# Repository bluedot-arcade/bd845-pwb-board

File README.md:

<p align="right">

</p>
<br><br>
<p align="center">
    <h1 align="center">BD845-PWB IO Board</h1>
    <p align="center">A clone of the original Konami GN845-PWB(B) Stage I/O board for DDR machines.</p>
    <p align="center"><strong><a href="https://github.com/bluedot-arcade/bd845-pwb-firmware">Go to firmware repository</a></strong></p>
    <p align="center"><strong><a href="https://docs.bluedotarcade.com/boards/bd845-pwb">Explore the docs</a></strong></p>
    <br><br>
</p>

<p align="center">A render of the board from the front.</p>

## About the project

The goal of the project is to replicate the original Konami GN845-PWB(B) Stage I/O board by designing a drop in replacement board for future-proofing DDR cabinets.

It emulates the original DDR Stage I/O communication protocol boot sequence allowing to run the game without an I/O Check Bypass. Other protocol features are currently not supported.

It also provides additional features such as debouncing and a Light-On-Press mode that lights up the arrow light when pressed without the need of an external lights driver board.

The board can be re-programmed with a custom/updated firmware. The latest version of the firmware can be found [here](https://github.com/bluedot-arcade/bd845-pwb-firmware).

For more information read the [docs](https://docs.bluedotarcade.com/boards/bd845-pwb).

<p align="right">(<a href="#readme-top">back to top</a>)</p>

## Project structure

* [/fab/](/fab/) - the files required for fabbrication that includes gerbers, drills and assembly files.
* [/kicad/](/kicad/) -  the kicad project files.
* [/images/](/images/) - images and renders.
* [/sch_bd845-pwb.pdf](/sch_bd845-pwb.pdf) - the board's schematic.
* [/draw_bd845-pwb.pdf](/draw_bd845-pwb.pdf) - the board's mechanical drawings.
* [/bom_bd845-pwb.csv](/bom_bd845-pwb.csv) - the board's bill of materials.
* [/ibom_bd845-pwb.html](/ibom_bd845-pwb.html) - an interactive bill of materials very useful for manual assembly.

<p align="right">(<a href="#readme-top">back to top</a>)</p>

## Images and renders

PCB Front layer:

PCB Back layer:

Original Konami GN845-PWB:

<p align="right">(<a href="#readme-top">back to top</a>)</p>

## License

Distributed under the CERN OHL S 2 License. See [LICENSE.txt] for more information.

<p align="right">(<a href="#readme-top">back to top</a>)</p>

## Acknowledgments

* [NaokiS] - for providing valuable information about the original DDR stage IO communication protocol.
* [Marco Ruggiero] - for designing the BlueDot logo and beta-testing the board on its own cabinet.
* [Mattia Pini] - for lending me his KSYS573 computer to carry out tests.
* [MameDev] - for opensourcing the KSYS573 Boot IO check emulation which this board is based on.
* [InteractiveHtmlBom] - the Kicad plugin used to generate the interactive BOM.
* [Kicad] - for allowing me to design this board for free!

<p align="right">(<a href="#readme-top">back to top</a>)</p>

[NaokiS]: http://nsaito.co.uk/
[Marco Ruggiero]: https://www.instagram.com/ruggiero.design/
[Mattia Pini]: https://github.com/martirius
[MameDev]: https://github.com/mamedev/mame/blob/master/src/mame/konami/ksys573.cpp
[InteractiveHtmlBom]: https://github.com/openscopeproject/InteractiveHtmlBom
[Kicad]: https://www.kicad.org/
[LICENSE.txt]: /LICENSE.txtschematic

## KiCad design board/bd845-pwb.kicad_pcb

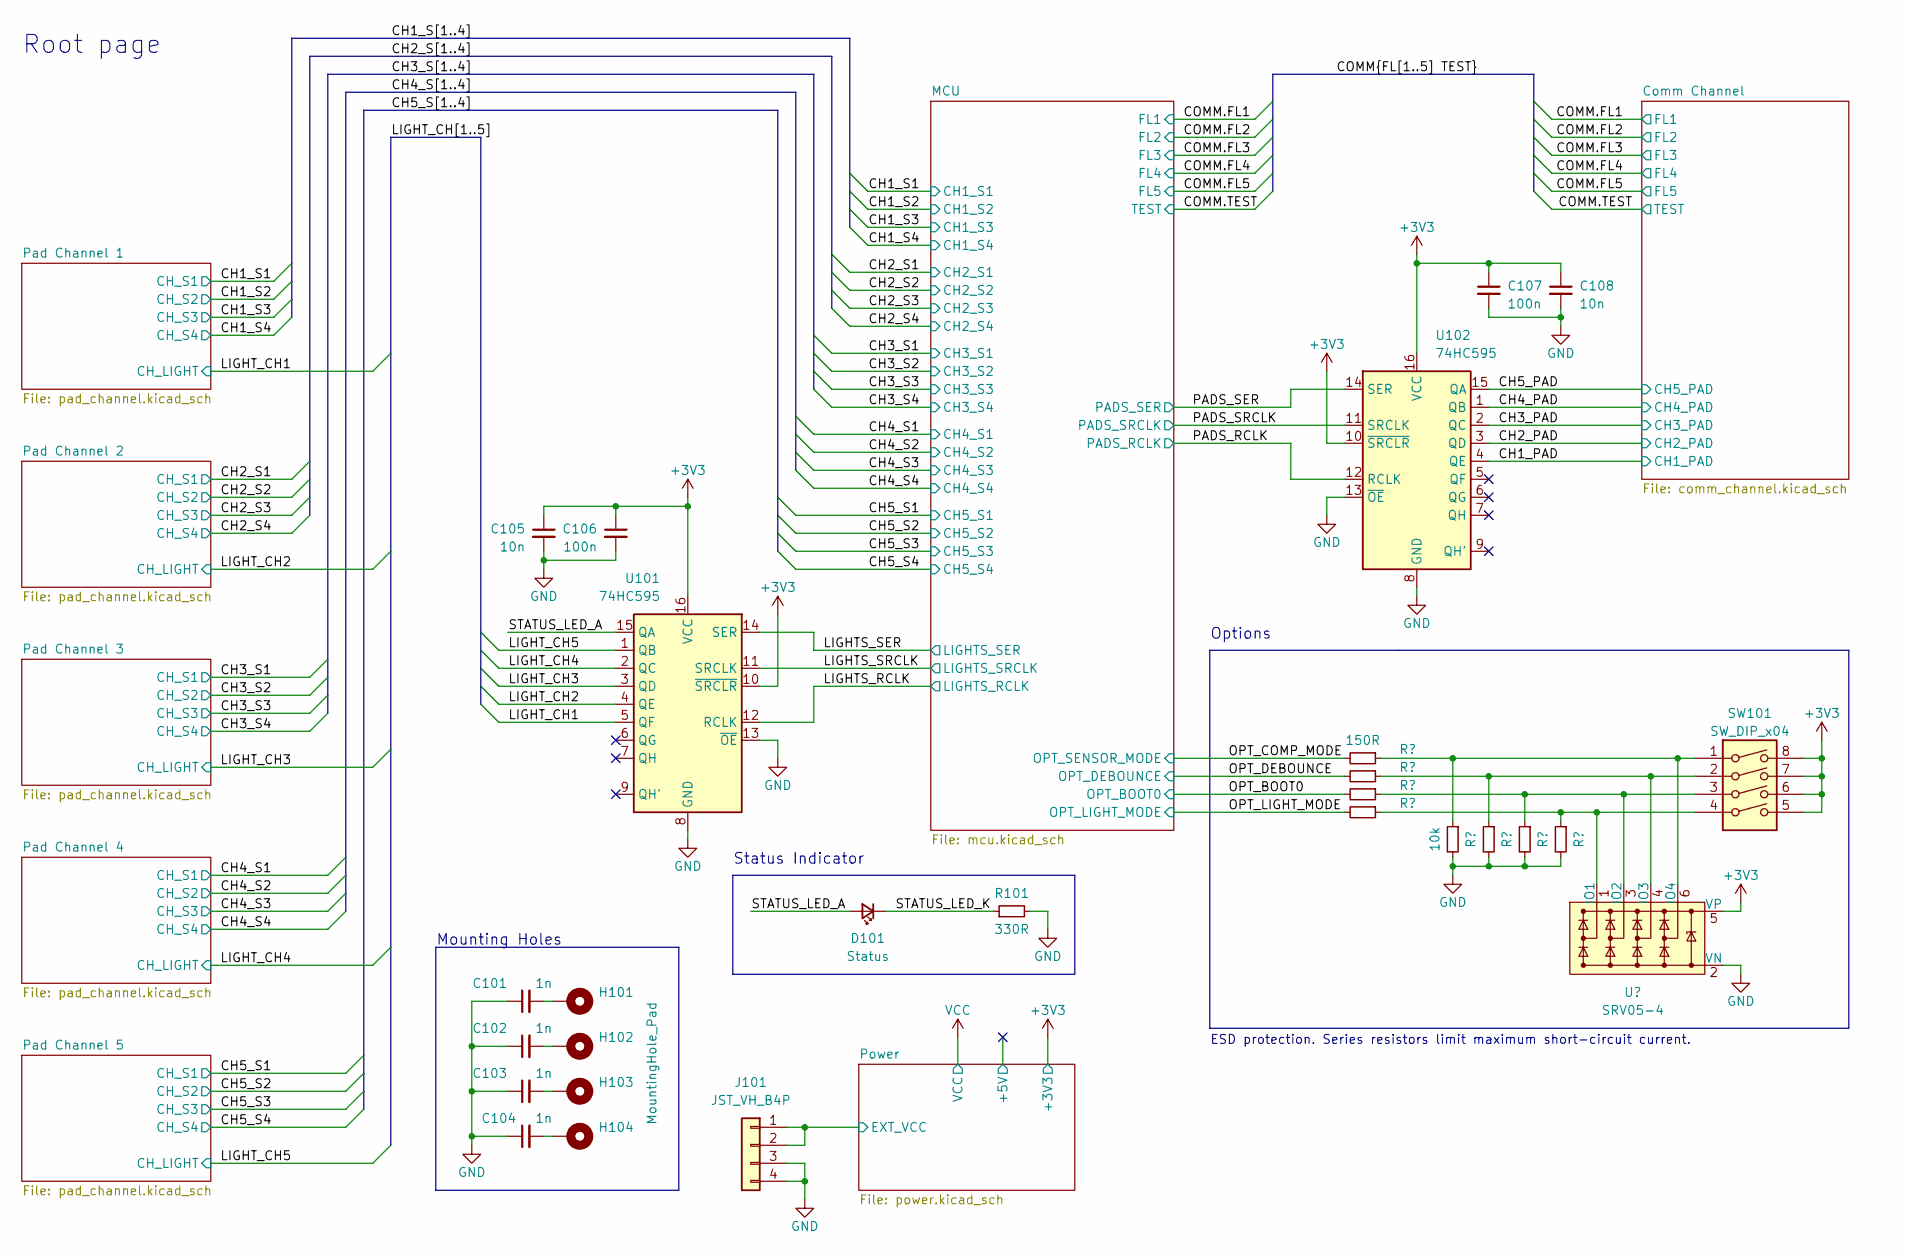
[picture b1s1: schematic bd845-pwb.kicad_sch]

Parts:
C101, C102, C103, C104: 1n; C_0603_1608Metric
C105, C108: 10n; C_0603_1608Metric
C106, C107: 100n; C_0603_1608Metric
D101: Status; LED_0805_2012Metric
H101, H102, H103, H104: MountingHole_Pad; MountingHole_4mm_Pad_Via
J101: JST_VH_B4P; JST_VH_B4P-VH_1x04_P3.96mm_Vertical
R101: 330R; R_0603_1608Metric
R102, R103, R104, R105: 150R; R_0603_1608Metric
R106, R107, R108, R109: 10k; R_0603_1608Metric
SW101: SW_DIP_x04; SW_DIP_SPSTx04_Slide_9.78x12.34mm_W7.62mm_P2.54mm
U101, U102: 74HC595; SO-16_3.9x9.9mm_P1.27mm
U103: SRV05-4; SOT-23-6

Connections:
+3V3: C105.1, C106.1, C107.1, C108.1, SW101.5, SW101.6, SW101.7, SW101.8, U101.10 (~SRCLR), U101.16 (VCC), U102.10 (~SRCLR), U102.16 (VCC), U103.5 (VP); also elsewhere on the board
/CH1_PAD: U102.4 (QE); also elsewhere on the board
/CH2_PAD: U102.3 (QD); also elsewhere on the board
/CH3_PAD: U102.2 (QC); also elsewhere on the board
/CH4_PAD: U102.1 (QB); also elsewhere on the board
/CH5_PAD: U102.15 (QA); also elsewhere on the board
/LIGHTS_RCLK: U101.12 (RCLK); also elsewhere on the board
/LIGHTS_SER: U101.14 (SER); also elsewhere on the board
/LIGHTS_SRCLK: U101.11 (SRCLK); also elsewhere on the board
/LIGHT_CH1: U101.5 (QF); also elsewhere on the board
/LIGHT_CH2: U101.4 (QE); also elsewhere on the board
/LIGHT_CH3: U101.3 (QD); also elsewhere on the board
/LIGHT_CH4: U101.2 (QC); also elsewhere on the board
/LIGHT_CH5: U101.1 (QB); also elsewhere on the board
/OPT_BOOT0: R104.2; also elsewhere on the board
/OPT_COMP_MODE: R102.2; also elsewhere on the board
/OPT_DEBOUNCE: R103.2; also elsewhere on the board
/OPT_LIGHT_MODE: R105.2; also elsewhere on the board
/PADS_RCLK: U102.12 (RCLK); also elsewhere on the board
/PADS_SER: U102.14 (SER); also elsewhere on the board
/PADS_SRCLK: U102.11 (SRCLK); also elsewhere on the board
/Power/EXT_VCC: J101.1, J101.2; also elsewhere on the board
/STATUS_LED_A: D101.2 (A), U101.15 (QA)
/STATUS_LED_K: D101.1 (K), R101.1
GND: C101.1, C102.1, C103.1, C104.1, C105.2, C106.2, C107.2, C108.2, J101.3, J101.4, R101.2, R106.2, R107.2, R108.2, R109.2, U101.8 (GND), U101.13 (~OE), U102.8 (GND), U102.13 (~OE), U103.2 (VN); also elsewhere on the board
unnamed: C101.2, H101.1
unnamed: C102.2, H102.1
unnamed: C103.2, H103.1
unnamed: C104.2, H104.1
unnamed: R105.1, R109.1, SW101.4, U103.1 (IO1)
unnamed: R104.1, R108.1, SW101.3, U103.3 (IO2)
unnamed: R103.1, R107.1, SW101.2, U103.4 (IO3)
unnamed: R102.1, R106.1, SW101.1, U103.6 (IO4)

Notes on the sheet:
ESD protection. Series resistors limit maximum short-circuit current.
Root page
Options
Status Indicator
Mounting Holes

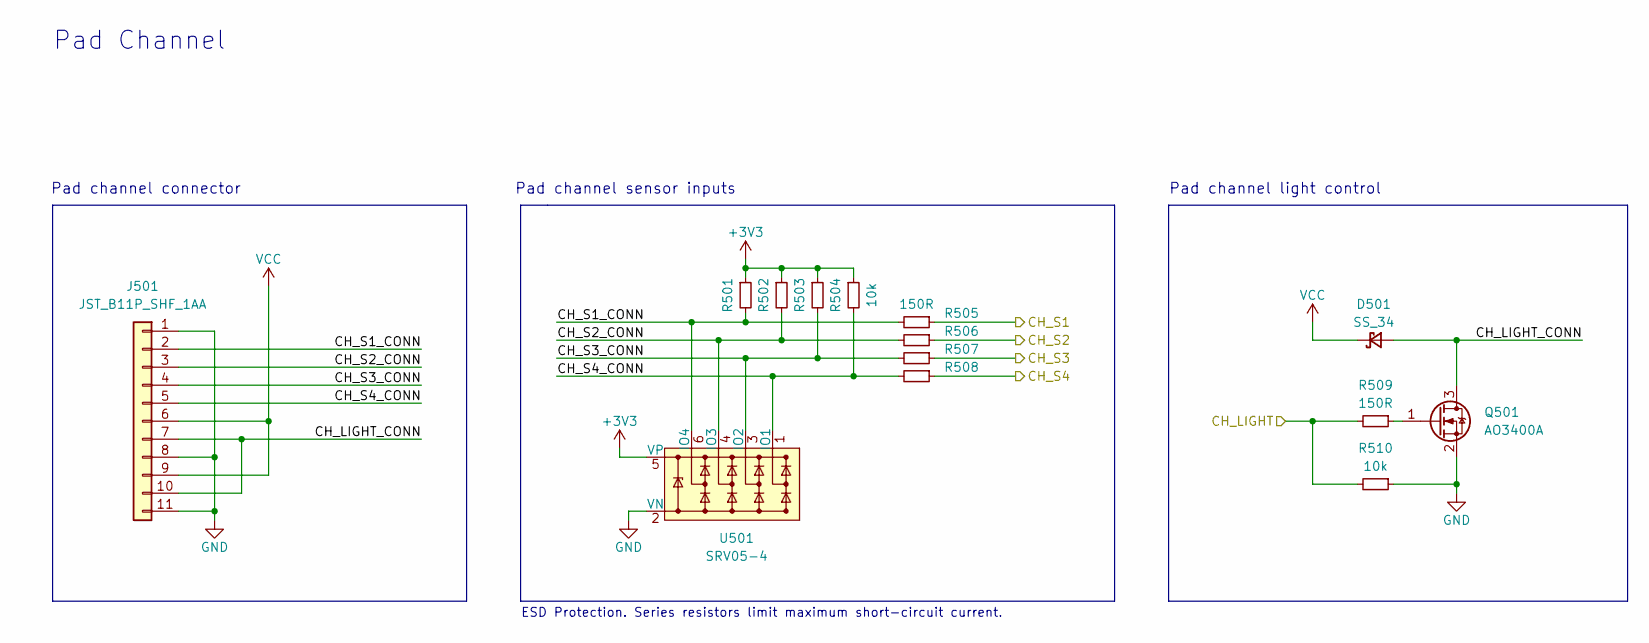
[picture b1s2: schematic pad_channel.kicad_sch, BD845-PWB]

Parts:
D501: SS_34; D_SMA
J501: JST_B11P_SHF_1AA; JST_NH_B11P-SHF-1AA_1x11_P2.50mm_Vertical
Q501: AO3400A; SOT-23
R501, R502, R503, R504, R510: 10k; R_0603_1608Metric
R505, R506, R507, R508, R509: 150R; R_0603_1608Metric
U501: SRV05-4; SOT-23-6

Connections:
+3V3: R501.1, R502.1, R503.1, R504.1, U501.5 (VP); also elsewhere on the board
/CH1_S1: R505.1; also elsewhere on the board
/CH1_S2: R506.1; also elsewhere on the board
/CH1_S3: R507.1; also elsewhere on the board
/CH1_S4: R508.1; also elsewhere on the board
/LIGHT_CH1: R509.2, R510.2; also elsewhere on the board
/Pad Channel 1/CH_LIGHT_CONN: D501.2 (A), J501.7, J501.10, Q501.3 (D)
/Pad Channel 1/CH_S1_CONN: J501.2, R501.2, R505.2, U501.6 (IO4)
/Pad Channel 1/CH_S2_CONN: J501.3, R502.2, R506.2, U501.4 (IO3)
/Pad Channel 1/CH_S3_CONN: J501.4, R503.2, R507.2, U501.3 (IO2)
/Pad Channel 1/CH_S4_CONN: J501.5, R504.2, R508.2, U501.1 (IO1)
GND: J501.1, J501.8, J501.11, Q501.2 (S), R510.1, U501.2 (VN); also elsewhere on the board
unnamed: Q501.1 (G), R509.1
VCC: D501.1 (K), J501.6, J501.9; also elsewhere on the board

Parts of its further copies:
D601, D701, D801, D901: SS_34; D_SMA
J901: JST_B11P_SHF_1AA; JST_NH_B11P-SHF-1AA_1x11_P2.50mm_Vertical
Q601, Q701, Q801, Q901: AO3400A; SOT-23
R601, R602, R603, R604, R610, R701, R702, R703, R704, R710, R801, R802, R803, R804, R810, R901, R902, R903, R904, R910: 10k; R_0603_1608Metric
R605, R606, R607, R608, R609, R705, R706, R707, R708, R709, R805, R806, R807, R808, R809, R905, R906, R907, R908, R909: 150R; R_0603_1608Metric
U601, U701, U801, U901: SRV05-4; SOT-23-6

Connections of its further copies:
+3V3: R601.1, R602.1, R603.1, R604.1, R701.1, R702.1, R703.1, R704.1, R801.1, R802.1, R803.1, R804.1, R901.1, R902.1, R903.1, R904.1, U601.5 (VP), U701.5 (VP), U801.5 (VP), U901.5 (VP); also elsewhere on the board
/CH2_S1: R605.1; also elsewhere on the board
/CH2_S2: R606.1; also elsewhere on the board
/CH2_S3: R607.1; also elsewhere on the board
/CH2_S4: R608.1; also elsewhere on the board
/CH3_S1: R705.1; also elsewhere on the board
/CH3_S2: R706.1; also elsewhere on the board
/CH3_S3: R707.1; also elsewhere on the board
/CH3_S4: R708.1; also elsewhere on the board
/CH4_S1: R805.1; also elsewhere on the board
/CH4_S2: R806.1; also elsewhere on the board
/CH4_S3: R807.1; also elsewhere on the board
/CH4_S4: R808.1; also elsewhere on the board
/CH5_S1: R905.1; also elsewhere on the board
/CH5_S2: R906.1; also elsewhere on the board
/CH5_S3: R907.1; also elsewhere on the board
/CH5_S4: R908.1; also elsewhere on the board
/LIGHT_CH2: R609.2, R610.2; also elsewhere on the board
/LIGHT_CH3: R709.2, R710.2; also elsewhere on the board
/LIGHT_CH4: R809.2, R810.2; also elsewhere on the board
/LIGHT_CH5: R909.2, R910.2; also elsewhere on the board
/Pad Channel 2/CH_LIGHT_CONN: D601.2 (A), Q601.3 (D); also elsewhere on the board
/Pad Channel 2/CH_S1_CONN: R601.2, R605.2, U601.6 (IO4); also elsewhere on the board
/Pad Channel 2/CH_S2_CONN: R602.2, R606.2, U601.4 (IO3); also elsewhere on the board
/Pad Channel 2/CH_S3_CONN: R603.2, R607.2, U601.3 (IO2); also elsewhere on the board
/Pad Channel 2/CH_S4_CONN: R604.2, R608.2, U601.1 (IO1); also elsewhere on the board
/Pad Channel 3/CH_LIGHT_CONN: D701.2 (A), Q701.3 (D); also elsewhere on the board
/Pad Channel 3/CH_S1_CONN: R701.2, R705.2, U701.6 (IO4); also elsewhere on the board
/Pad Channel 3/CH_S2_CONN: R702.2, R706.2, U701.4 (IO3); also elsewhere on the board
/Pad Channel 3/CH_S3_CONN: R703.2, R707.2, U701.3 (IO2); also elsewhere on the board
/Pad Channel 3/CH_S4_CONN: R704.2, R708.2, U701.1 (IO1); also elsewhere on the board
/Pad Channel 4/CH_LIGHT_CONN: D801.2 (A), Q801.3 (D); also elsewhere on the board
/Pad Channel 4/CH_S1_CONN: R801.2, R805.2, U801.6 (IO4); also elsewhere on the board
/Pad Channel 4/CH_S2_CONN: R802.2, R806.2, U801.4 (IO3); also elsewhere on the board
/Pad Channel 4/CH_S3_CONN: R803.2, R807.2, U801.3 (IO2); also elsewhere on the board
/Pad Channel 4/CH_S4_CONN: R804.2, R808.2, U801.1 (IO1); also elsewhere on the board
/Pad Channel 5/CH_LIGHT_CONN: D901.2 (A), J901.7, J901.10, Q901.3 (D)
/Pad Channel 5/CH_S1_CONN: J901.2, R901.2, R905.2, U901.6 (IO4)
/Pad Channel 5/CH_S2_CONN: J901.3, R902.2, R906.2, U901.4 (IO3)
/Pad Channel 5/CH_S3_CONN: J901.4, R903.2, R907.2, U901.3 (IO2)
/Pad Channel 5/CH_S4_CONN: J901.5, R904.2, R908.2, U901.1 (IO1)
GND: J901.1, J901.8, J901.11, Q601.2 (S), Q701.2 (S), Q801.2 (S), Q901.2 (S), R610.1, R710.1, R810.1, R910.1, U601.2 (VN), U701.2 (VN), U801.2 (VN), U901.2 (VN); also elsewhere on the board
unnamed: Q601.1 (G), R609.1
unnamed: Q701.1 (G), R709.1
unnamed: Q801.1 (G), R809.1
unnamed: Q901.1 (G), R909.1
VCC: D601.1 (K), D701.1 (K), D801.1 (K), D901.1 (K), J901.6, J901.9; also elsewhere on the board

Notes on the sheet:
Pad channel connector
ESD Protection. Series resistors limit maximum short-circuit current.
Pad channel sensor inputs
Pad Channel
Pad channel light control

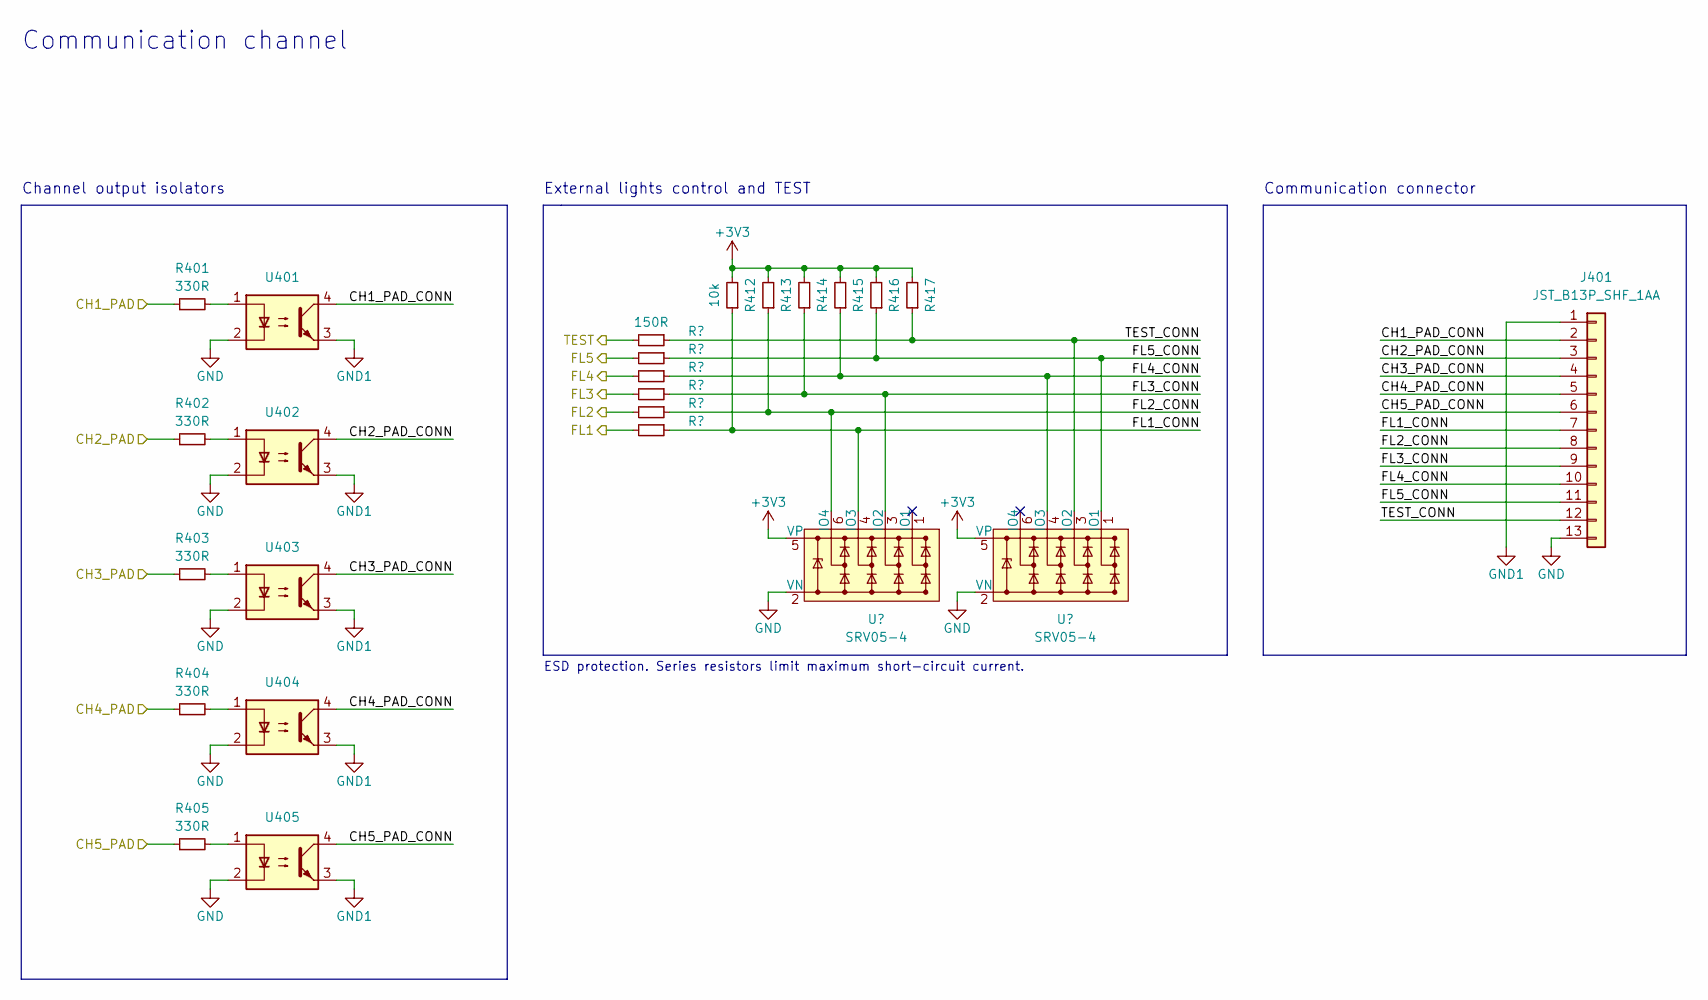
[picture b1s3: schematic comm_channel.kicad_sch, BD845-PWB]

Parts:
J401: JST_B13P_SHF_1AA; JST_NH_B13P-SHF-1AA_1x13_P2.50mm_Vertical
R401, R402, R403, R404, R405: 330R; R_0603_1608Metric
R406, R407, R408, R409, R410, R411: 150R; R_0603_1608Metric
R412, R413, R414, R415, R416, R417: 10k; R_0603_1608Metric
U401, U402, U403, U404, U405: EL357N(C)(TA)-G; SO-4_4.4x3.6mm_P2.54mm
U406, U407: SRV05-4; SOT-23-6

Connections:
+3V3: R412.2, R413.2, R414.2, R415.2, R416.2, R417.2, U406.5 (VP), U407.5 (VP); also elsewhere on the board
/CH1_PAD: R401.1; also elsewhere on the board
/CH2_PAD: R402.1; also elsewhere on the board
/CH3_PAD: R403.1; also elsewhere on the board
/CH4_PAD: R404.1; also elsewhere on the board
/CH5_PAD: R405.1; also elsewhere on the board
/COMM.FL1: R411.2; also elsewhere on the board
/COMM.FL2: R410.2; also elsewhere on the board
/COMM.FL3: R409.2; also elsewhere on the board
/COMM.FL4: R408.2; also elsewhere on the board
/COMM.FL5: R407.2; also elsewhere on the board
/COMM.TEST: R406.2; also elsewhere on the board
/Comm Channel/CH1_PAD_CONN: J401.2, U401.4
/Comm Channel/CH2_PAD_CONN: J401.3, U402.4
/Comm Channel/CH3_PAD_CONN: J401.4, U403.4
/Comm Channel/CH4_PAD_CONN: J401.5, U404.4
/Comm Channel/CH5_PAD_CONN: J401.6, U405.4
/Comm Channel/FL1_CONN: J401.7, R411.1, R412.1, U406.4 (IO3)
/Comm Channel/FL2_CONN: J401.8, R410.1, R413.1, U406.6 (IO4)
/Comm Channel/FL3_CONN: J401.9, R409.1, R414.1, U406.3 (IO2)
/Comm Channel/FL4_CONN: J401.10, R408.1, R415.1, U407.4 (IO3)
/Comm Channel/FL5_CONN: J401.11, R407.1, R416.1, U407.1 (IO1)
/Comm Channel/TEST_CONN: J401.12, R406.1, R417.1, U407.3 (IO2)
GND: J401.13, U401.2, U402.2, U403.2, U404.2, U405.2, U406.2 (VN), U407.2 (VN); also elsewhere on the board
GND1: J401.1, U401.3, U402.3, U403.3, U404.3, U405.3
unnamed: R401.2, U401.1
unnamed: R402.2, U402.1
unnamed: R403.2, U403.1
unnamed: R404.2, U404.1
unnamed: R405.2, U405.1

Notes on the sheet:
Communication connector
Channel output isolators
Communication channel
External lights control and TEST
ESD protection. Series resistors limit maximum short-circuit current.

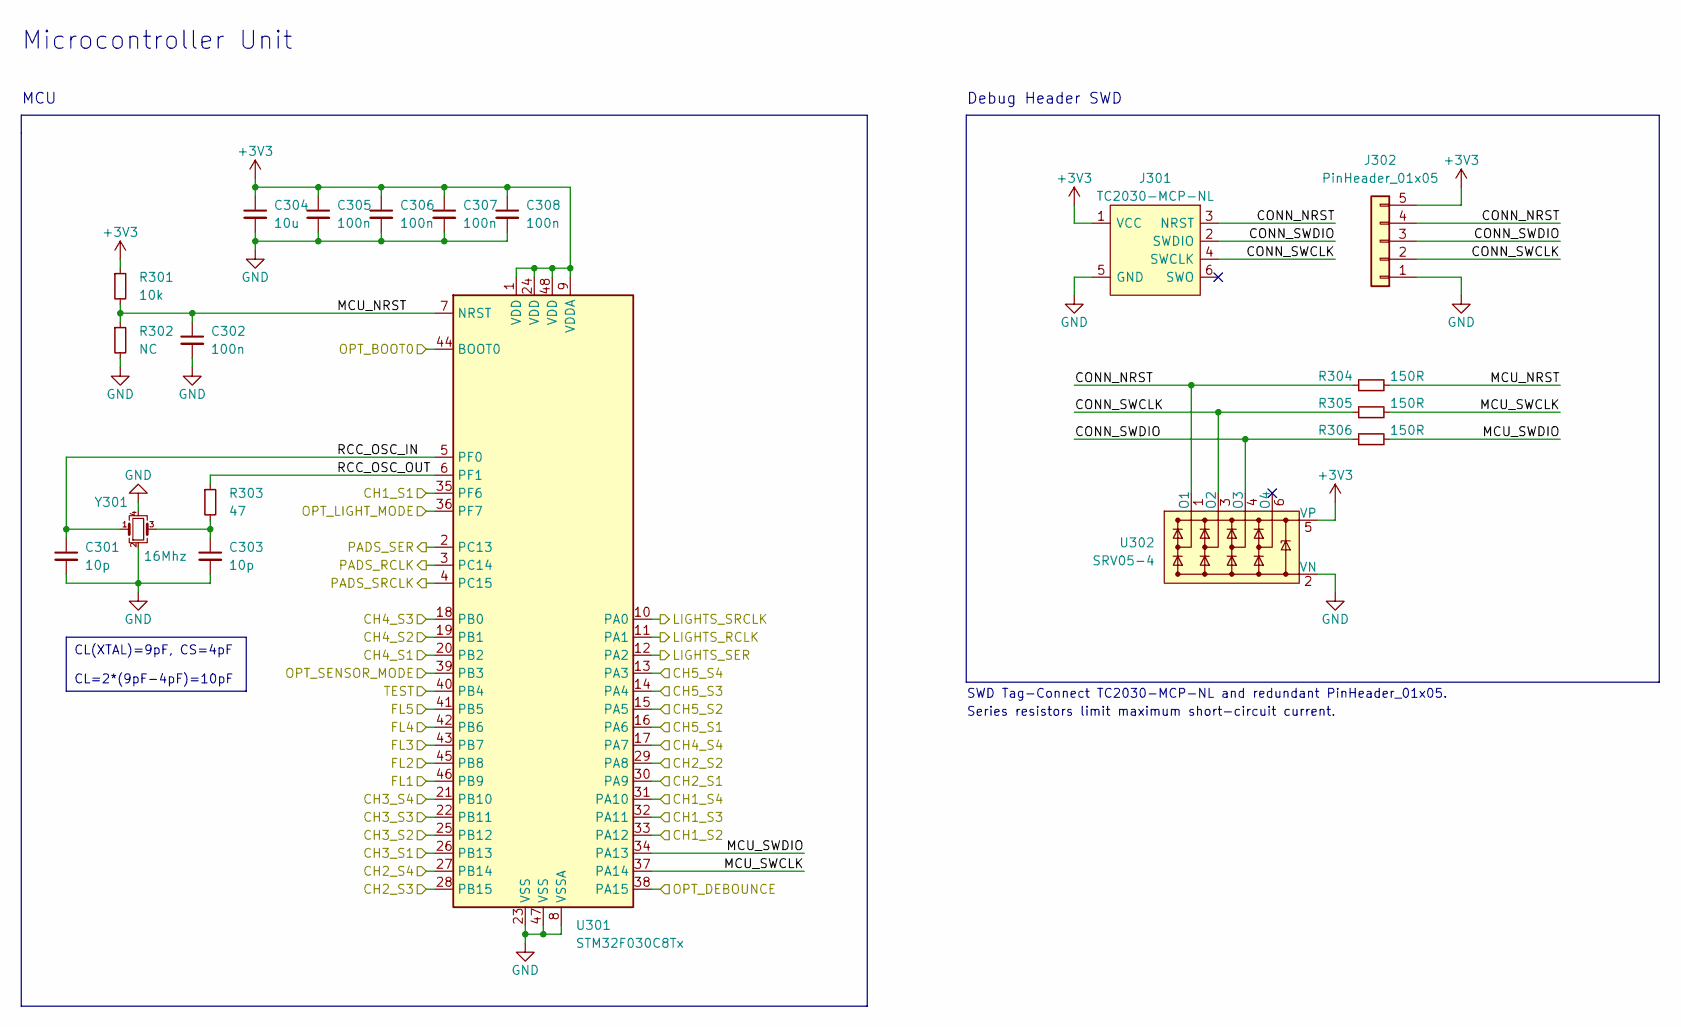
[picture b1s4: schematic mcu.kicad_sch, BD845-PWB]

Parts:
C301, C303: 10p; C_0603_1608Metric
C302, C305, C306, C307, C308: 100n; C_0603_1608Metric
C304: 10u; C_0603_1608Metric
J301: TC2030-MCP-NL; Tag-Connect_TC2030-IDC-NL_2x03_P1.27mm_Vertical; Manufacturer_Part_Number TC2030-MCP-NL; Mouser Part Number 579-TC2030-MCP-NL
J302: PinHeader_01x05; PinHeader_1x05_P2.54mm_Vertical
R301: 10k; R_0603_1608Metric
R302: NC; R_0603_1608Metric
R303: 47; R_0603_1608Metric
R304, R305, R306: 150R; R_0603_1608Metric
U301: STM32F030C8Tx; LQFP-48_7x7mm_P0.5mm
U302: SRV05-4; SOT-23-6
Y301: 16Mhz; Crystal_SMD_3225-4Pin_3.2x2.5mm

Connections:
+3V3: C304.1, C305.1, C306.1, C307.1, C308.1, J301.1 (VCC), J302.5, R301.1, U301.1 (VDD), U301.9 (VDDA), U301.24 (VDD), U301.48 (VDD), U302.5 (VP); also elsewhere on the board
/CH1_S1: U301.35 (PF6); also elsewhere on the board
/CH1_S2: U301.33 (PA12); also elsewhere on the board
/CH1_S3: U301.32 (PA11); also elsewhere on the board
/CH1_S4: U301.31 (PA10); also elsewhere on the board
/CH2_S1: U301.30 (PA9); also elsewhere on the board
/CH2_S2: U301.29 (PA8); also elsewhere on the board
/CH2_S3: U301.28 (PB15); also elsewhere on the board
/CH2_S4: U301.27 (PB14); also elsewhere on the board
/CH3_S1: U301.26 (PB13); also elsewhere on the board
/CH3_S2: U301.25 (PB12); also elsewhere on the board
/CH3_S3: U301.22 (PB11); also elsewhere on the board
/CH3_S4: U301.21 (PB10); also elsewhere on the board
/CH4_S1: U301.20 (PB2); also elsewhere on the board
/CH4_S2: U301.19 (PB1); also elsewhere on the board
/CH4_S3: U301.18 (PB0); also elsewhere on the board
/CH4_S4: U301.17 (PA7); also elsewhere on the board
/CH5_S1: U301.16 (PA6); also elsewhere on the board
/CH5_S2: U301.15 (PA5); also elsewhere on the board
/CH5_S3: U301.14 (PA4); also elsewhere on the board
/CH5_S4: U301.13 (PA3); also elsewhere on the board
/COMM.FL1: U301.46 (PB9); also elsewhere on the board
/COMM.FL2: U301.45 (PB8); also elsewhere on the board
/COMM.FL3: U301.43 (PB7); also elsewhere on the board
/COMM.FL4: U301.42 (PB6); also elsewhere on the board
/COMM.FL5: U301.41 (PB5); also elsewhere on the board
/COMM.TEST: U301.40 (PB4); also elsewhere on the board
/LIGHTS_RCLK: U301.11 (PA1); also elsewhere on the board
/LIGHTS_SER: U301.12 (PA2); also elsewhere on the board
/LIGHTS_SRCLK: U301.10 (PA0); also elsewhere on the board
/MCU/CONN_NRST: J301.3 (NRST), J302.4, R304.1, U302.1 (IO1)
/MCU/CONN_SWCLK: J301.4 (SWCLK), J302.2, R305.1, U302.3 (IO2)
/MCU/CONN_SWDIO: J301.2 (SWDIO), J302.3, R306.1, U302.4 (IO3)
/MCU/MCU_NRST: C302.1, R301.2, R302.1, R304.2, U301.7 (NRST)
/MCU/MCU_SWCLK: R305.2, U301.37 (PA14)
/MCU/MCU_SWDIO: R306.2, U301.34 (PA13)
/MCU/RCC_OSC_IN: C301.1, U301.5 (PF0), Y301.1
/MCU/RCC_OSC_OUT: R303.1, U301.6 (PF1)
/OPT_BOOT0: U301.44 (BOOT0); also elsewhere on the board
/OPT_COMP_MODE: U301.39 (PB3); also elsewhere on the board
/OPT_DEBOUNCE: U301.38 (PA15); also elsewhere on the board
/OPT_LIGHT_MODE: U301.36 (PF7); also elsewhere on the board
/PADS_RCLK: U301.3 (PC14); also elsewhere on the board
/PADS_SER: U301.2 (PC13); also elsewhere on the board
/PADS_SRCLK: U301.4 (PC15); also elsewhere on the board
GND: C301.2, C302.2, C303.2, C304.2, C305.2, C306.2, C307.2, C308.2, J301.5 (GND), J302.1, R302.2, U301.8 (VSSA), U301.23 (VSS), U301.47 (VSS), U302.2 (VN), Y301.2, Y301.4; also elsewhere on the board
unnamed: C303.1, R303.2, Y301.3

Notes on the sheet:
CL(XTAL)=9pF, CS=4pF CL=2*(9pF-4pF)=10pF
Series resistors limit maximum short-circuit current.
SWD Tag-Connect TC2030-MCP-NL and redundant PinHeader_01x05.
MCU
Microcontroller Unit
Debug Header SWD

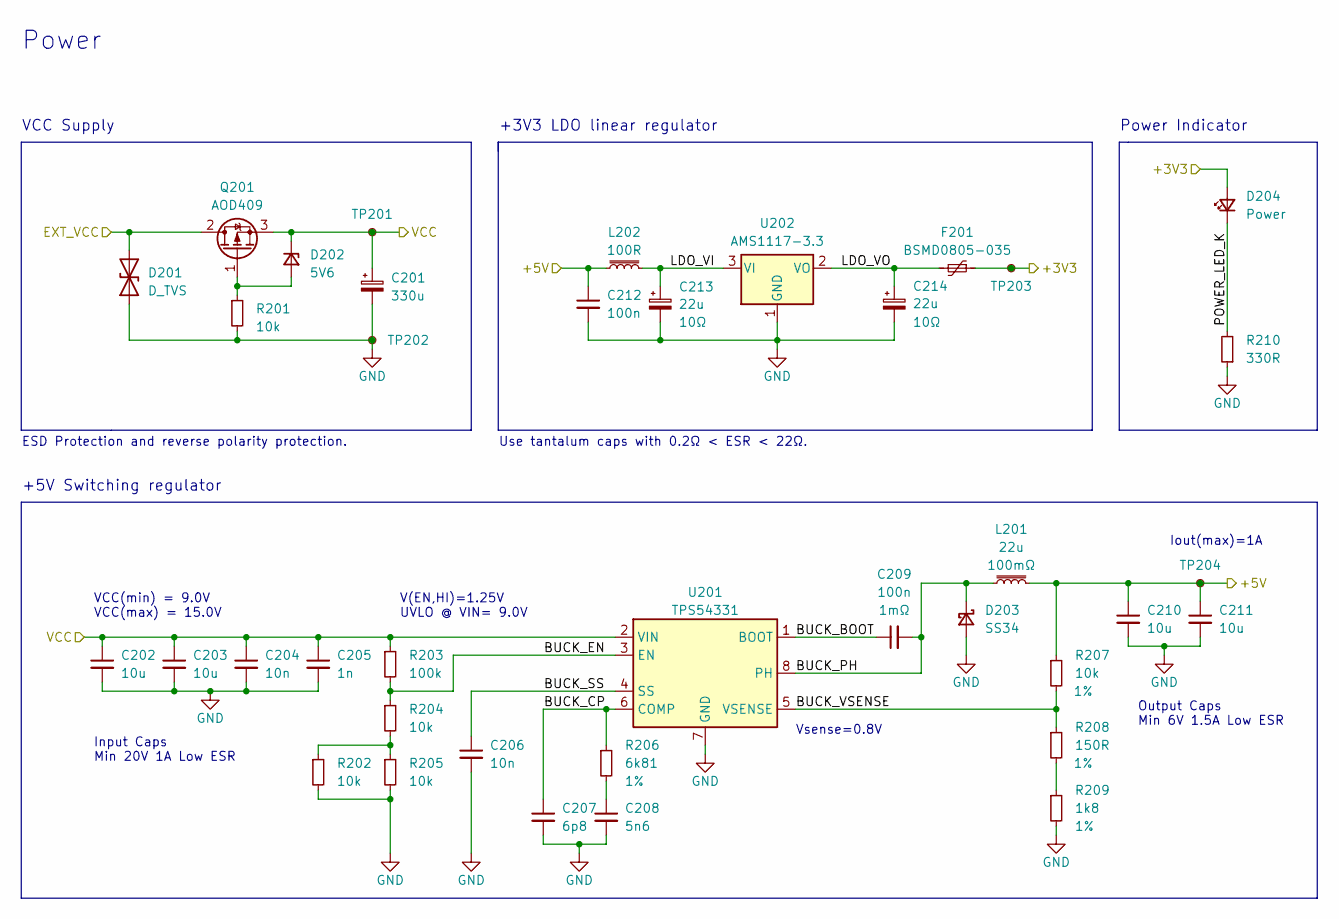
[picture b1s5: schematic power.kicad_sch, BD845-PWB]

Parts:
C201: 330u; CP_Radial_D8.0mm_P3.50mm
C202, C203, C210, C211: 10u; C_0603_1608Metric
C204, C206: 10n; C_0603_1608Metric
C205: 1n; C_0603_1608Metric
C207: 6p8; C_0603_1608Metric
C208: 5n6; C_0603_1608Metric
C209, C212: 100n; C_0603_1608Metric
C213, C214: 22u; CP_EIA-3528-15_AVX-H
D201: D_TVS; D_SMA
D202: 5V6; D_MiniMELF
D203: SS34; D_SMA
D204: Power; LED_0805_2012Metric
F201: BSMD0805-035; Fuse_0805_2012Metric
L201: 22u; L_Taiyo-Yuden_NR-50xx
L202: 100R; R_0805_2012Metric
Q201: AOD409; TO-252-3_TabPin2
R201, R202, R204, R205, R207: 10k; R_0603_1608Metric
R203: 100k; R_0603_1608Metric
R206: 6k81; R_0603_1608Metric
R208: 150R; R_0603_1608Metric
R209: 1k8; R_0603_1608Metric
R210: 330R; R_0603_1608Metric
TP201, TP202, TP203, TP204: TestPoint_Small; TestPoint_Pad_D1.0mm
U201: TPS54331; SOIC-8_3.9x4.9mm_P1.27mm
U202: AMS1117-3.3; SOT-223-3_TabPin2

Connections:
+3V3: D204.2 (A), F201.1, TP203.1; also elsewhere on the board
/Power/+5V: C210.1, C211.1, C212.1, L201.2, L202.1, R207.1, TP204.1
/Power/BUCK_BOOT: C209.1, U201.1 (BOOT)
/Power/BUCK_CP: C207.1, R206.1, U201.6 (COMP)
/Power/BUCK_EN: R203.2, R204.1, U201.3 (EN)
/Power/BUCK_PH: C209.2, D203.1 (K), L201.1, U201.8 (PH)
/Power/BUCK_SS: C206.1, U201.4 (SS)
/Power/BUCK_VSENSE: R207.2, R208.1, U201.5 (VSENSE)
/Power/EXT_VCC: D201.2 (A2), Q201.2 (D); also elsewhere on the board
/Power/LDO_VI: C213.1, L202.2, U202.3 (VI)
/Power/LDO_VO: C214.1, F201.2, U202.2 (VO)
/Power/POWER_LED_K: D204.1 (K), R210.2
GND: C201.2, C202.2, C203.2, C204.2, C205.2, C206.2, C207.2, C208.2, C210.2, C211.2, C212.2, C213.2, C214.2, D201.1 (A1), D203.2 (A), R201.2, R202.2, R205.2, R209.2, R210.1, TP202.1, U201.7 (GND), U202.1 (GND); also elsewhere on the board
unnamed: C208.1, R206.2
unnamed: D202.2 (A), Q201.1 (G), R201.1
unnamed: R202.1, R204.2, R205.1
unnamed: R208.2, R209.1
VCC: C201.1, C202.1, C203.1, C204.1, C205.1, D202.1 (K), Q201.3 (S), R203.1, TP201.1, U201.2 (VIN); also elsewhere on the board

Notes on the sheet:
Power Indicator
+3V3 LDO linear regulator
Iout(max)=1A
VCC(min) = 9.0V VCC(max) = 15.0V
+5V Switching regulator
V(EN,HI)=1.25V UVLO @ VIN= 9.0V
Output Caps Min 6V 1.5A Low ESR
Vsense=0.8V
Use tantalum caps with 0.2Ω < ESR < 22Ω.
ESD Protection and reverse polarity protection.
VCC Supply
Input Caps Min 20V 1A Low ESR
Power

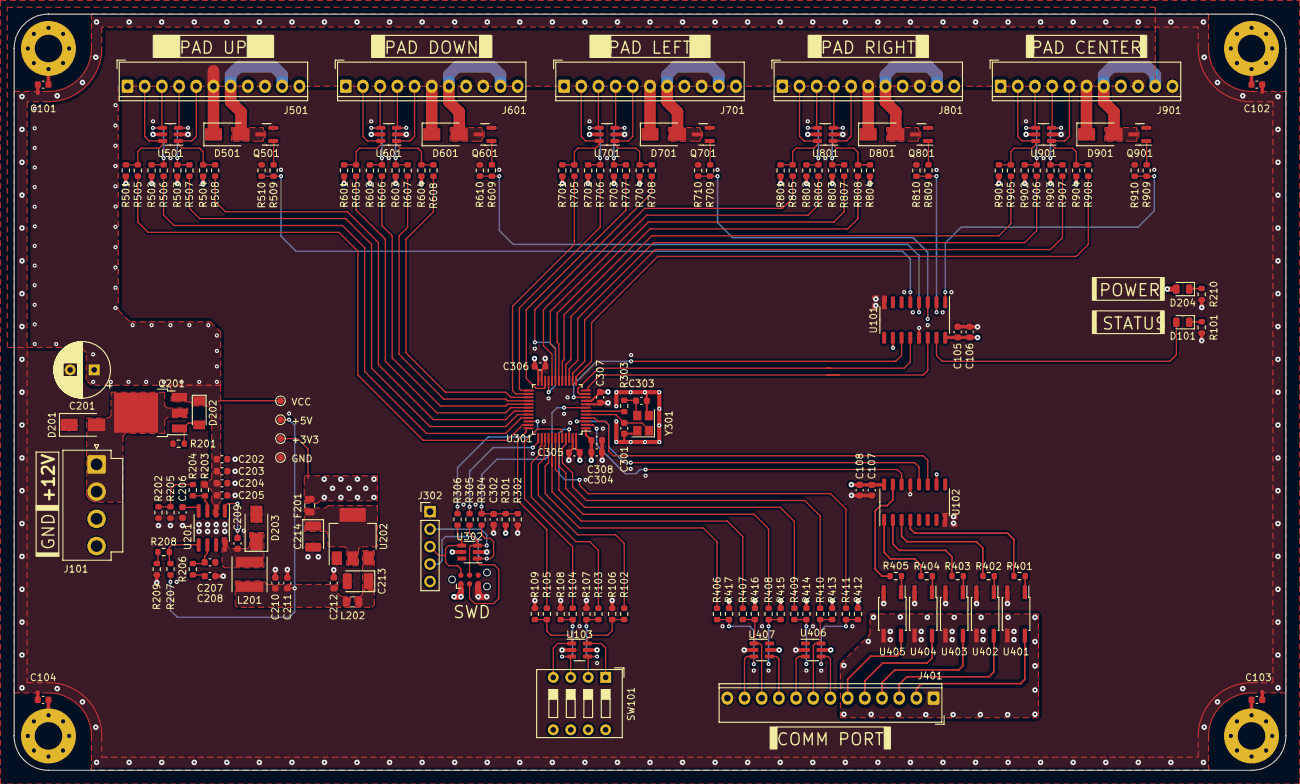
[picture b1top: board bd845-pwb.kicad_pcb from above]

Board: 4 copper layers, 185.0 x 110.0 mm, 179 parts (0 on the bottom side), 130 nets.

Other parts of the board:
J601, J701, J801: JST_B11P_XH_A; JST_NH_B11P-SHF-1AA_1x11_P2.50mm_Vertical

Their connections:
/Pad Channel 2/CH_LIGHT_CONN: J601.7, J601.10; also elsewhere on the board
/Pad Channel 2/CH_S1_CONN: J601.2; also elsewhere on the board
/Pad Channel 2/CH_S2_CONN: J601.3; also elsewhere on the board
/Pad Channel 2/CH_S3_CONN: J601.4; also elsewhere on the board
/Pad Channel 2/CH_S4_CONN: J601.5; also elsewhere on the board
/Pad Channel 3/CH_LIGHT_CONN: J701.7, J701.10; also elsewhere on the board
/Pad Channel 3/CH_S1_CONN: J701.2; also elsewhere on the board
/Pad Channel 3/CH_S2_CONN: J701.3; also elsewhere on the board
/Pad Channel 3/CH_S3_CONN: J701.4; also elsewhere on the board
/Pad Channel 3/CH_S4_CONN: J701.5; also elsewhere on the board
/Pad Channel 4/CH_LIGHT_CONN: J801.7, J801.10; also elsewhere on the board
/Pad Channel 4/CH_S1_CONN: J801.2; also elsewhere on the board
/Pad Channel 4/CH_S2_CONN: J801.3; also elsewhere on the board
/Pad Channel 4/CH_S3_CONN: J801.4; also elsewhere on the board
/Pad Channel 4/CH_S4_CONN: J801.5; also elsewhere on the board
GND: J601.1, J601.8, J601.11, J701.1, J701.8, J701.11, J801.1, J801.8, J801.11; also elsewhere on the board
VCC: J601.6, J601.9, J701.6, J701.9, J801.6, J801.9; also elsewhere on the board

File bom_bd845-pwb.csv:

"Reference","Value","Footprint","Datasheet","Accuracy","Description","ESR","Manufacturer_Name","Manufacturer_Part_Number","Qty"
"C101-C104, C205","1n","Capacitor_SMD:C_0603_1608Metric","~","","","","","","5"
"C105, C108, C204, C206","10n","Capacitor_SMD:C_0603_1608Metric","~","","","","","","4"
"C106, C107, C209, C212, C302, C305-C308","100n","Capacitor_SMD:C_0603_1608Metric","~","","","-- mixed values --","","","9"
"C201","330u","Capacitor_THT:CP_Radial_D8.0mm_P3.50mm","~","","","","","","1"
"C202, C203, C210, C211, C304","10u","Capacitor_SMD:C_0603_1608Metric","~","","","","","","5"
"C207","6p8","Capacitor_SMD:C_0603_1608Metric","~","","","","","","1"
"C208","5n6","Capacitor_SMD:C_0603_1608Metric","~","","","","","","1"
"C213, C214","22u","Capacitor_Tantalum_SMD:CP_EIA-3528-15_AVX-H","~","","","10Ω","","","2"
"C301, C303","10p","Capacitor_SMD:C_0603_1608Metric","~","","","","","","2"
"D101","Status","LED_SMD:LED_0805_2012Metric","~","","","","","","1"
"D201","SMAJ15CA","Diode_SMD:D_SMA","~","","","","","","1"
"D202","5V6","Diode_SMD:D_MiniMELF","~","","","","","","1"
"D203, D501, D601, D701, D801, D901","SS34","Diode_SMD:D_SMA","~","","","","","","6"
"D204","Power","LED_SMD:LED_0805_2012Metric","~","","","","","","1"
"F201, F501, F601, F701, F801, F901","BSMD1206-150-16V","Fuse:Fuse_1206_3216Metric_Pad1.42x1.75mm_HandSolder","~","","","","","","6"
"F202","BSMD0805-035","Fuse:Fuse_0805_2012Metric","~","","","","","","1"
"H101-H104","MountingHole_Pad","MountingHole:MountingHole_4mm_Pad_Via","~","","","","","","4"
"J101","JST_VH_B4P","Connector_JST:JST_VH_B4P-VH_1x04_P3.96mm_Vertical","~","","","","","","1"
"J301","TC2030-MCP-NL","Connector:Tag-Connect_TC2030-IDC-NL_2x03_P1.27mm_Vertical","http://ww1.microchip.com/downloads/en/DeviceDoc/TC2030-MCP-N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","","TC2030-MCP-NL PCB Footprint (no legs)","","Microchip","TC2030-MCP-NL","1"
"J302","PinHeader_01x05","Connector_PinHeader_2.54mm:PinHeader_1x05_P2.54mm_Vertical","~","","","","","","1"
"J401","JST_B13P_SHF_1AA","ProjectLibrary:JST_NH_B13P-SHF-1AA_1x13_P2.50mm_Vertical","~","","","","","","1"
"J501, J601, J701, J801, J901","JST_B11P_SHF_1AA","ProjectLibrary:JST_NH_B11P-SHF-1AA_1x11_P2.50mm_Vertical","~","","","","","","5"
"L201","22u","Inductor_SMD:L_Taiyo-Yuden_NR-50xx","~","","","100mΩ","","","1"
"L202","100R","Resistor_SMD:R_0805_2012Metric","~","","","","","","1"
"Q201","AOD409","Package_TO_SOT_SMD:TO-252-3_TabPin2","https://datasheet.lcsc.com/lcsc/1811091710_Alpha---Omega-Sem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","","","","","","1"
"Q501, Q601, Q701, Q801, Q901","AO3400A","Package_TO_SOT_SMD:SOT-23","http://www.aosmd.com/pdfs/datasheet/AO3400A.pdf","","","","","","5"
"R101, R210, R401-R405","330R","Resistor_SMD:R_0603_1608Metric","~","","","","","","7"
"R102-R105, R208, R304-R306, R406-R411, R505-R509, R605-R609, R705-R709, R805-R809, R905-R909","150R","Resistor_SMD:R_0603_1608Metric","~","-- mixed values --","","","","","39"
"R106-R109, R201, R202, R204, R205, R207, R301, R412-R417, R501-R504, R510, R601-R604, R610, R701-R704, R710, R801-R804, R810, R901-R904, R910","10k","Resistor_SMD:R_0603_1608Metric","~","-- mixed values --","","","","","41"
"R203","100k","Resistor_SMD:R_0603_1608Metric","~","","","","","","1"
"R206","6k8","Resistor_SMD:R_0603_1608Metric","~","1%","","","","","1"
"R209","1k8","Resistor_SMD:R_0603_1608Metric","~","1%","","","","","1"
"R302","NC","Resistor_SMD:R_0603_1608Metric","~","","","","","","1"
"R303","47R","Resistor_SMD:R_0603_1608Metric","~","","","","","","1"
"SW101","SW_DIP_x04","Button_Switch_THT:SW_DIP_SPSTx04_Slide_9.78x12.34mm_W7.62mm_P2.54mm","~","","","","","","1"
"TP201-TP204","TestPoint_Small","TestPoint:TestPoint_Pad_D1.0mm","~","","","","","","4"
"U101, U102","74HC595","Package_SO:SO-16_3.9x9.9mm_P1.27mm","http://www.ti.com/lit/ds/symlink/sn74hc595.pdf","","","","","","2"
"U103, U302, U406, U407, U501, U601, U701, U801, U901","SRV05-4","Package_TO_SOT_SMD:SOT-23-6","http://www.onsemi.com/pub/Collateral/SRV05-4-D.PDF","","","","","","9"
"U201","TPS54331","Package_SO:SOIC-8_3.9x4.9mm_P1.27mm","https://www.ti.com/lit/ds/symlink/tps54331.pdf","","","","","","1"
"U202","AMS1117-3.3","Package_TO_SOT_SMD:SOT-223-3_TabPin2","http://www.advanced-monolithic.com/pdf/ds1117.pdf","","","","","","1"
"U301","STM32F030C8Tx","Package_QFP:LQFP-48_7x7mm_P0.5mm","http://www.st.com/st-web-ui/static/active/en/resource/techni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","","","","","","1"
"U401-U405","EL357N(C)(TA)-G","Package_SO:SO-4_4.4x3.6mm_P2.54mm","https://datasheet.lcsc.com/lcsc/1810271030_Everlight-Elec-EL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","","","","","","5"
"Y301","16Mhz","Crystal:Crystal_SMD_3225-4Pin_3.2x2.5mm","~","","","","","","1"

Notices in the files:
README.md:
https://img.shields.io/badge/license-CERN
